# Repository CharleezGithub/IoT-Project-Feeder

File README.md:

External Arduino Libraries used:

https://www.arduinolibraries.info/libraries/speedy-stepper

https://www.arduinolibraries.info/libraries/liquid-crystal_i2-c

https://www.arduinolibraries.info/libraries/esp32-time

Internal Libraries Used:

time.h

WebServer.h

HardwareSerial.h

WiFi.h

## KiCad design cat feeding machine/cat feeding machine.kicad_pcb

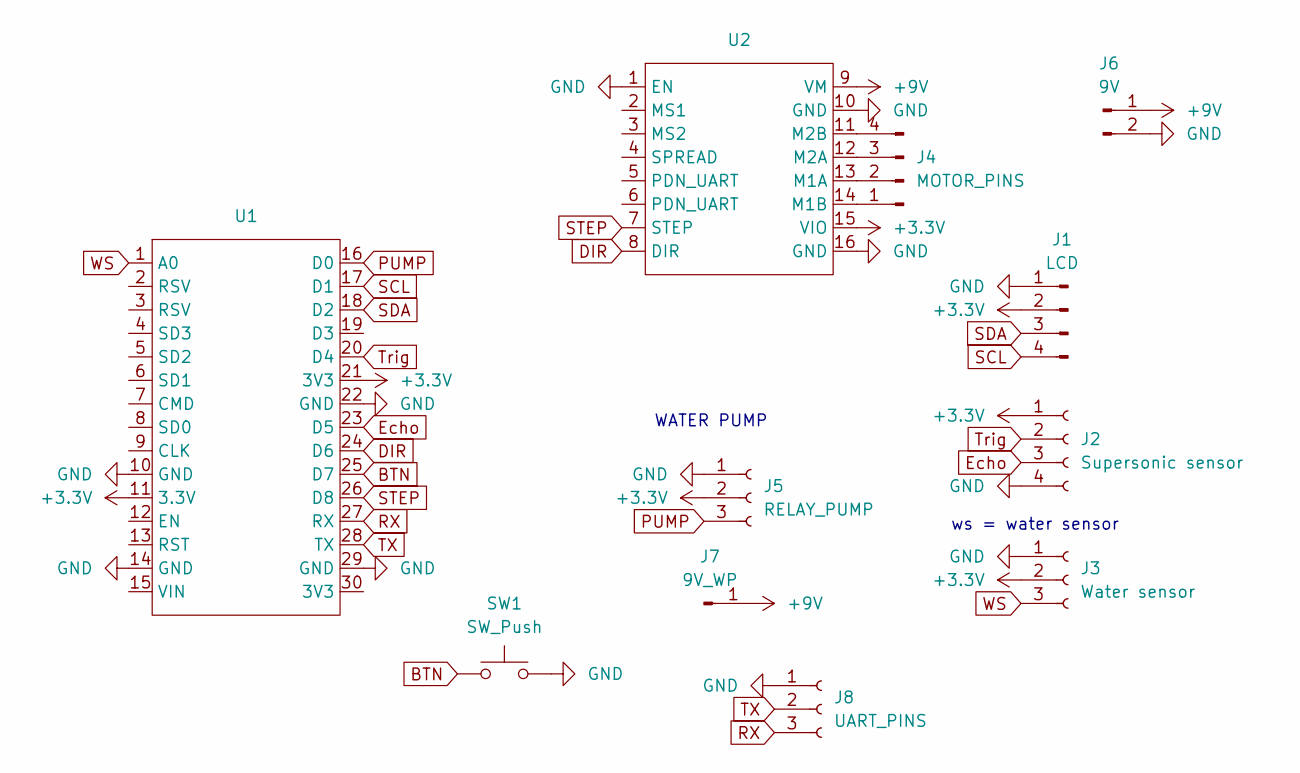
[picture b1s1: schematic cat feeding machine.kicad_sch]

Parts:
J1: LCD; PinHeader_1x04_P2.54mm_Vertical
J2: Supersonic sensor; PinHeader_1x04_P2.54mm_Vertical
J3: Water sensor; PinHeader_1x03_P2.54mm_Vertical
J4: MOTOR_PINS; PinHeader_1x04_P2.54mm_Vertical
J5: RELAY_PUMP; PinHeader_1x03_P2.54mm_Vertical
J6: 9V; PinHeader_1x02_P2.54mm_Vertical
J7: 9V_WP; PinHeader_1x01_P2.54mm_Vertical
J8: UART_PINS; PinHeader_1x03_P2.54mm_Vertical
SW1: SW_Push; SW_PUSH_6mm
U1: ESP8266_HOMEMADE
U2: TMC2209_homemade

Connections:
+3.3V: J1.2, J2.1, J3.2, J5.2, U1.11 (3.3V), U1.21 (3V3), U2.15 (VIO)
+9V: J6.1, J7.1 (Pin_1_1), U2.9 (VM)
BTN: SW1.1, U1.25 (D7)
DIR: U1.24 (D6), U2.8 (DIR)
Echo: J2.3, U1.23 (D5)
GND: J1.1, J2.4, J3.1, J5.1, J6.2, J8.1, SW1.2, U1.10 (GND), U1.14 (GND), U1.22 (GND), U1.29 (GND), U2.1 (EN), U2.10 (GND), U2.16 (GND)
unnamed: J4.1, U2.14 (M1B)
unnamed: J4.2, U2.13 (M1A)
unnamed: J4.3, U2.12 (M2A)
unnamed: J4.4, U2.11 (M2B)
PUMP: J5.3, U1.16 (D0)
RX: J8.3, U1.27 (RX)
SCL: J1.4, U1.17 (D1)
SDA: J1.3, U1.18 (D2)
STEP: U1.26 (D8), U2.7 (STEP)
TX: J8.2, U1.28 (TX)
Trig: J2.2, U1.20 (D4)
WS: J3.3, U1.1 (A0)

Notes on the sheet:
ws = water sensor
WATER PUMP

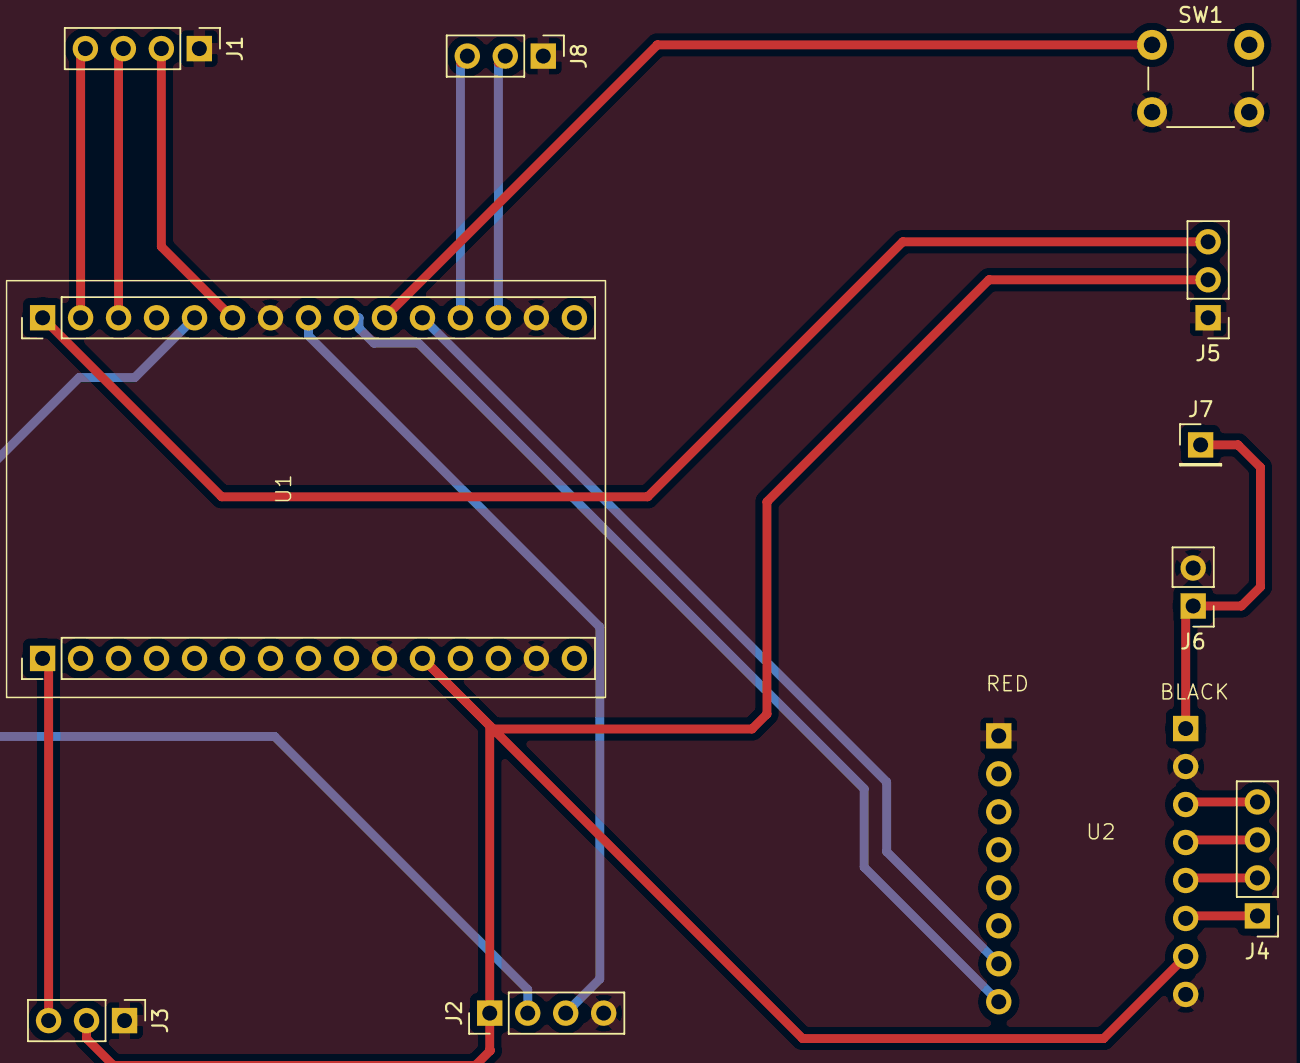
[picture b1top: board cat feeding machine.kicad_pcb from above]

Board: 2 copper layers, 11 parts (0 on the bottom side), 18 nets.

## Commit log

2026-04-09 ultra sonic food capacity left sensor
2026-04-09 water monitor
2026-04-16 restructure
2026-04-23 Adding stepper motor
    Moving files outside subfolder
    + adding the code for the stepper motor
2026-04-23 imported webserver example
2026-04-23 stuff n things that are mayhaps printed
2026-04-23 making folders
2026-04-23 Rename baseNew.stl to CAD/baseNew.stl
2026-04-23 Rename food container v1.stl to CAD/food container v1.stl
2026-04-23 Rename spiral.stl to CAD/spiral.stl
2026-04-23 Rename spiral container.stl to CAD/spiral container.stl
2026-04-23 StepperMotor update
    Changed the StepperMotorCode to use a class instead.
    Allows for changing pins and max weight
2026-04-23 connecting everything together
2026-04-23 webserver esp8266 working
2026-04-23 ultra sonic fix namespace byte collision
2026-04-23 correct precentage reporting
2026-04-30 added more support
2026-04-30 Fixes
    Fixed speed and acceleration of stepper motor.
    Made changes to the ultra-sonic sensor to allow for LCD-display
    Started code for LCD-display
2026-04-30 Water Pump
    Finished the water pump
2026-04-30 updated webserver that runs in parrallel a seperate esp exchanging data with the original esp through uart
2026-04-30 Finished LCD
    Finished the code for the LCD display.
2026-04-30 poster
2026-04-30 RTC for webserver
2026-05-01 final project assembly. webserver does not work
2026-05-01 finalized assembly and motor control
2026-05-03 PCB design, by Abdellah and Zhentao
2026-05-14 Document Arduino libraries in README
    Added a list of external and internal Arduino libraries used in the project.
2026-05-14 Update README with external and internal libraries
2026-05-14 Changes to water-pump
